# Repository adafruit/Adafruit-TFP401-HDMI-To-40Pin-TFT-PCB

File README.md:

## Adafruit TFP401 HDMI Decoder Breakout PCB
&nbsp; <br />
Click to purchase from the Adafruit Shop:
- [TFP401 HDMI/DVI Decoder to 40-Pin TTL Breakout - Without Touch](https://www.adafruit.com/product/2218)
- [TFP401 HDMI/DVI Decoder to 40-Pin TTL Breakout - With Touch](https://www.adafruit.com/product/2219)

It's a mini HDMI decoder board! So small and simple, you can use this board as an all-in-one display driver for TTL displays, or perhaps decoding HDMI/DVI video for some other project. This breakout features the TFP401 for decoding video, and for the touch version, an AR1100 USB resistive touch screen driver.

The TFP401 is a beefy DVI/HDMI decoder from TI. It can take unencrypted video and pipe out the raw 24-bit color pixel data - HDCP not supported! It will decode any resolution from 25-165MHz pixel clock, basically up to 1080p. We've used this breakout with 800x480 displays, so we have not specifically tested it with higher resolutions. We added a bunch of supporting circuitry like a backlight driver and configured it for running basic TTL display panels such as the ones we have in the shop

There are two versions, one is video only and one is video+touch. 

PCB Files for the Adafruit TFP401 HDMI Decoder Breakout. The format is EagleCAD schematic and board layout

For more details, check out the product pages at
- http://www.adafruit.com/products/2218
- http://www.adafruit.com/products/2219

### License

Adafruit invests time and resources providing this open source design, please support Adafruit and open-source hardware by [purchasing products from Adafruit](https://www.adafruit.com)!

All text above must be included in any redistribution

Designed by Limor Fried/Ladyada for Adafruit Industries.
Creative Commons Attribution/Share-Alike, all text above must be included in any redistribution. 
See license.txt for additional information.

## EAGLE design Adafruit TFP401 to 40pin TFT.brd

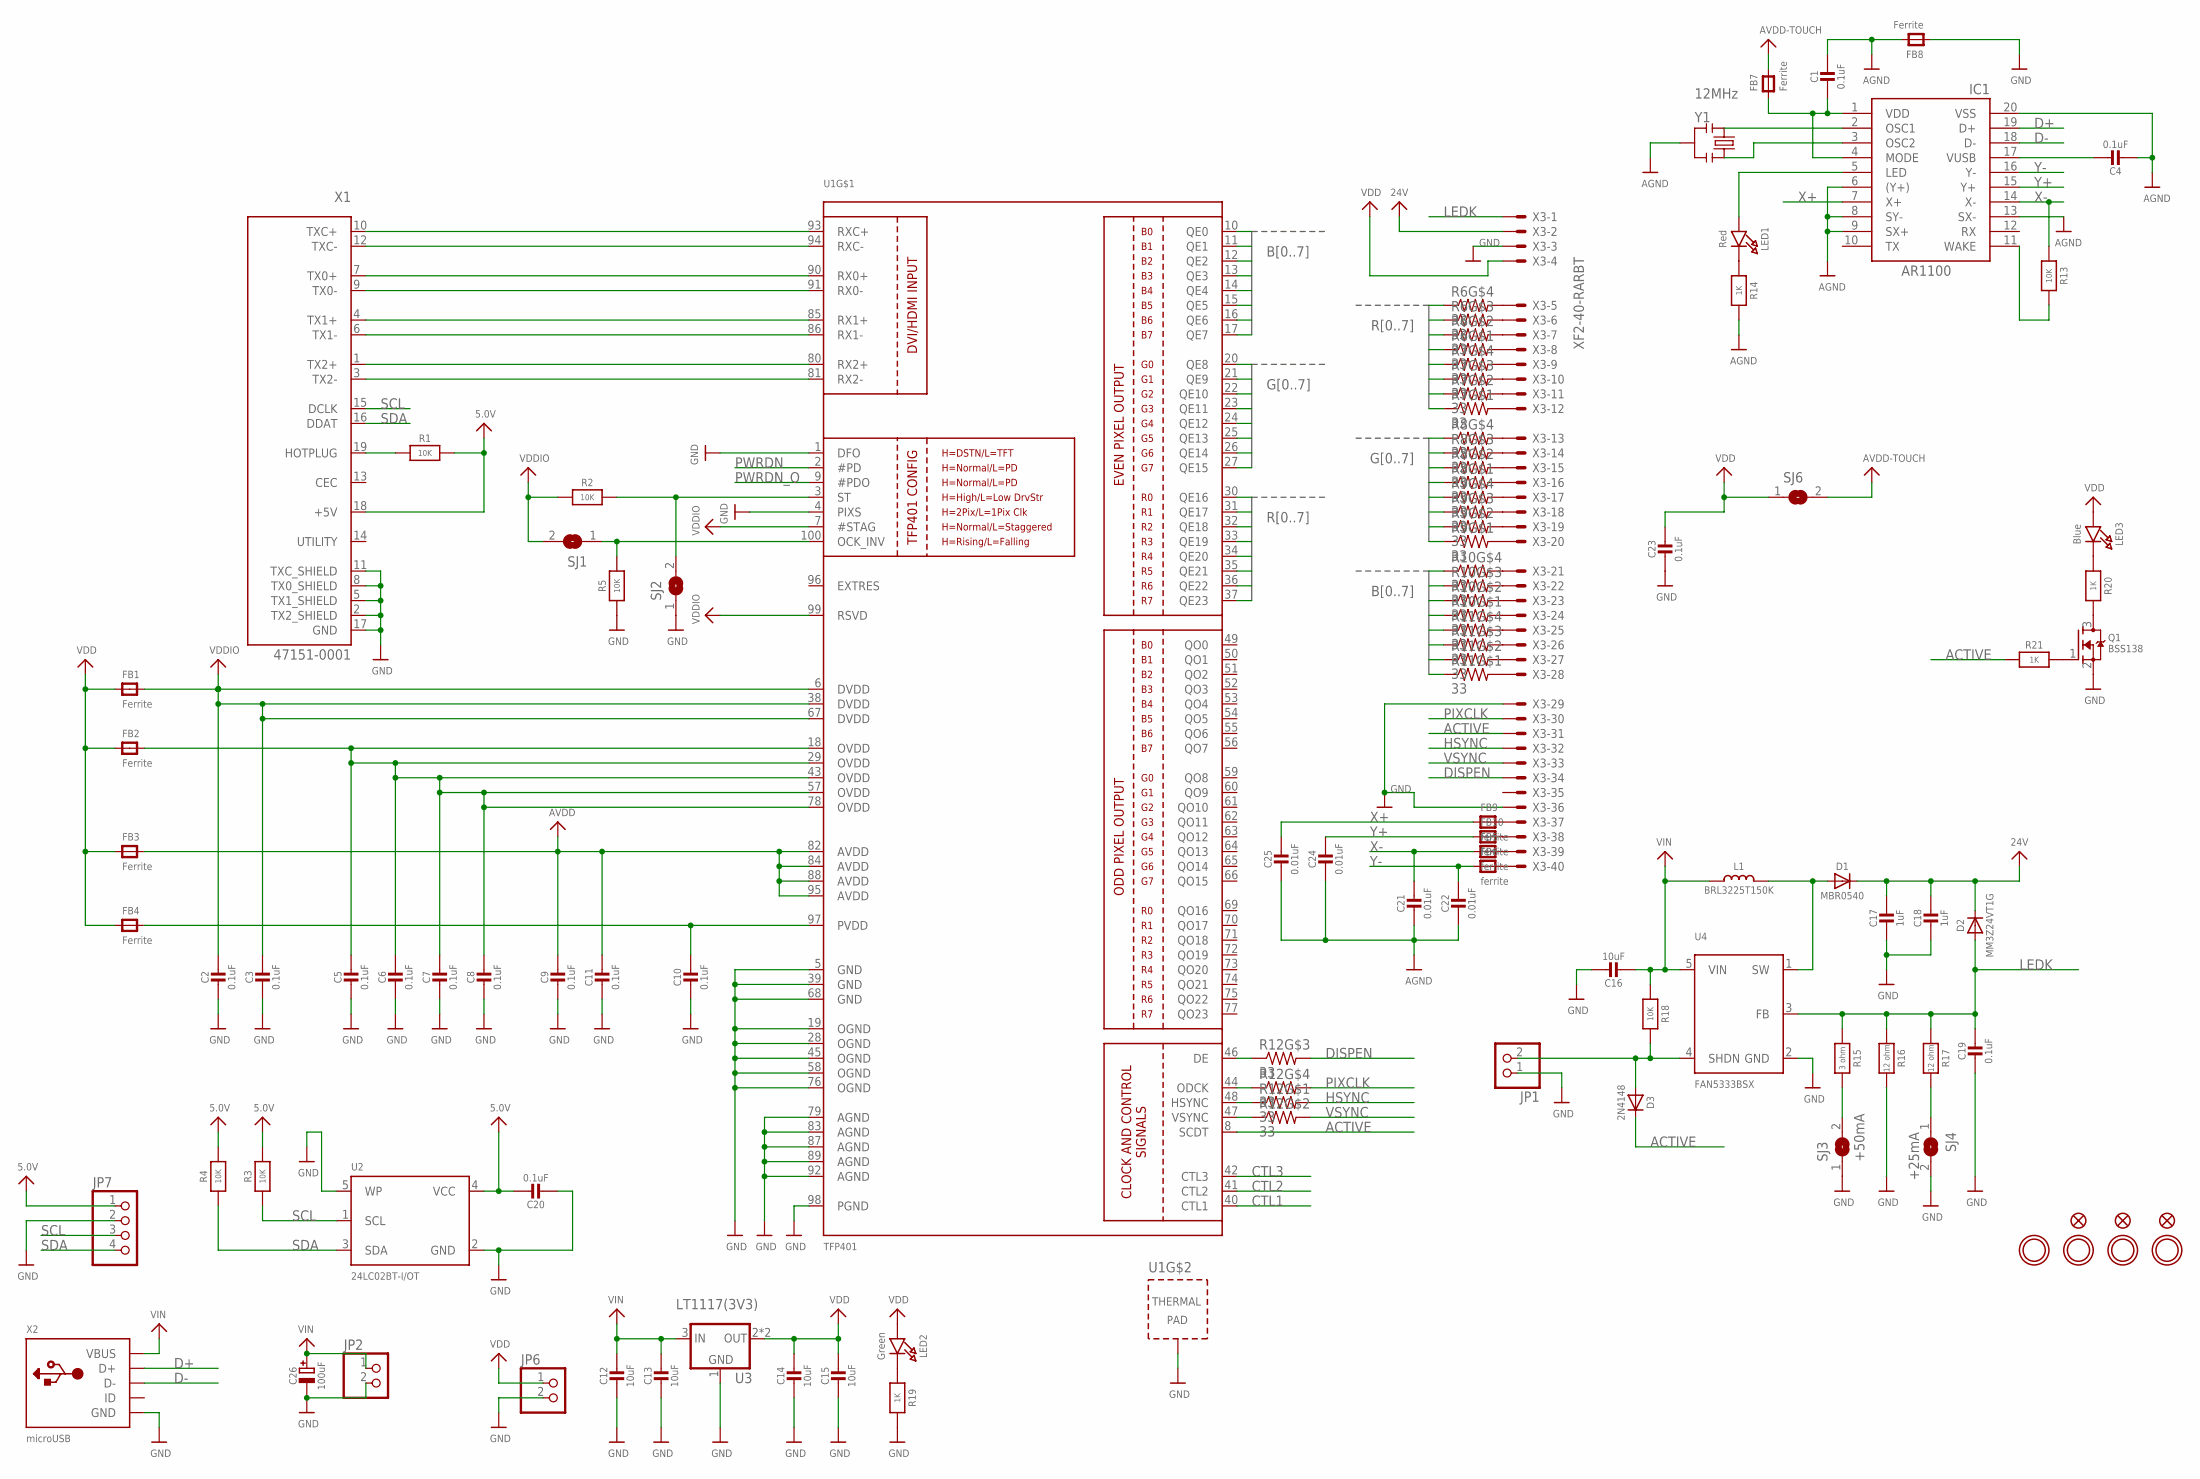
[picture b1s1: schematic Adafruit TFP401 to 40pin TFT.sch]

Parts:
C1, C2, C3, C4, C5, C7, C8, C9, C10, C11, C19, C20, C23: 0.1uF; 0805-NO
C6: 0.1uF; _0805MP
C12, C13, C14, C15, C16: 10uF; 0805-NO
C17, C18: 1uF; 0805-NO
C21, C22, C24, C25: 0.01uF; 0805-NO
C26: 100uF; PANASONIC_C
D1: MBR0540; SOD-123
D2: MM3Z24VT1G; SMADIODE
D3: 2N4148; SOD-323
FB1, FB2, FB3, FB4, FB7, FB8: Ferrite; _0805MP
FB5, FB6, FB9, FB10: ferrite; _0805MP
FID1, FID2, FID3: FIDUCIAL""; FIDUCIAL_1MM
IC1: AR1100_SSOP; TSSOP20-5.3MMBODY
JP1, JP2, JP6: HEADER-1X2ROUND; 1X02_ROUND
JP7: HEADER-1X476MIL; 1X04_ROUND_76
L1: BRL3225T150K; INDUCTOR_5X5MM_NR5040_NOTHERMALS
LED1: Red; CHIPLED_0805_NOOUTLINE
LED2: Green; CHIPLED_0805_NOOUTLINE
LED3: Blue; CHIPLED_0805_NOOUTLINE
Q1: BSS138; SOT23-R
R1, R2, R3, R4, R18: 10K; 0805-NO
R5, R13: 10K; _0805MP
R6, R7, R8, R9, R10, R11, R12: 33; RESPACK_4X0603
R14, R19, R20, R21: 1K; 0805-NO
R15: 3 ohm; 0805-NO
R16, R17: 12 ohm; 0805-NO
SJ1, SJ2: SOLDERJUMPER; SOLDERJUMPER_ARROW_NOPASTE
SJ3: +50mA; SOLDERJUMPER_ARROW_NOPASTE
SJ4: +25mA; SOLDERJUMPER_ARROW_NOPASTE
SJ6: SOLDERJUMPERCLOSED; SOLDERJUMPER_CLOSEDWIRE
U1: TFP401; S-PQFP-G100
U2: 24LC02BT-I/OT; SOT23-5
U3: LT1117(3V3); SOT223-R
U4: FAN5333BSX; SOT23-5
U$31, U$32, U$33, U$34: MOUNTINGHOLE3.0; MOUNTINGHOLE_3.0_PLATED
X1: 47151-0001; HDMI_MOLEX_47151-0001_DIMLAYER
X2: microUSB; 4UCONN_20329
X3: XF2-40-RARBT; 4-1734839-0
Y1: 12MHz; RESONATOR-SMD

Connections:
5.0V: C20.1, JP7.1, R1.2, R3.2, R4.2, U2.4 (VCC), X1.18 (+5V)
24V: C17.1, C18.1, D1.C, D2.C, X3.2 (MS)
ACTIVE: D3.C, R21.1, U1.8 (SCDT), X3.31 (MS)
AGND: C1.1, C4.2, C21.2, C22.2, C24.2, C25.2, FB8.2, IC1.6 ((Y+)), IC1.8 (SY-), IC1.9 (SX+), IC1.13 (SX-), IC1.20 (VSS), R14.2, Y1.2
ASD: R12.3 (1), U1.46 (DE)
AVDD: C9.1, C11.1, FB3.2, U1.82 (AVDD), U1.84 (AVDD), U1.88 (AVDD), U1.95 (AVDD)
AVDD2: FB7.2, SJ6.2
B0: R10.4 (1), U1.10 (QE0)
B1: R10.3 (1), U1.11 (QE1)
B2: R10.2 (1), U1.12 (QE2)
B3: R10.1, U1.13 (QE3)
B4: R11.4 (1), U1.14 (QE4)
B5: R11.3 (1), U1.15 (QE5)
B6: R11.2 (1), U1.16 (QE6)
B7: R11.1, U1.17 (QE7)
CTL1: U1.40 (CTL1)
CTL2: U1.41 (CTL2)
CTL3: U1.42 (CTL3)
CVB: R12.2 (1), U1.47 (VSYNC)
D+: IC1.19 (D+), X2.D+
D-: IC1.18 (D-), X2.D-
DISPEN: R12.6 (2), X3.34 (MS)
G0: R8.4 (1), U1.20 (QE8)
G1: R8.3 (1), U1.21 (QE9)
G2: R8.2 (1), U1.22 (QE10)
G3: R8.1, U1.23 (QE11)
G4: R9.4 (1), U1.24 (QE12)
G5: R9.3 (1), U1.25 (QE13)
G6: R9.2 (1), U1.26 (QE14)
G7: R9.1, U1.27 (QE15)
GND: C2.2, C3.2, C5.2, C6.2, C7.2, C8.2, C9.2, C10.2, C11.2, C12.2, C13.2, C14.2, C15.2, C16.1, C17.2, C18.2, C19.2, C20.2, C23.2, C26.-, FB8.1, JP1.1, JP2.2, JP6.2, JP7.2, Q1.2 (S), R5.1, R16.2, R19.2, SJ2.1, SJ3.1, SJ4.2, U1.1 (DFO), U1.4 (PIXS), U1.5 (GND), U1.19 (OGND), U1.28 (OGND), U1.39 (GND), U1.45 (OGND), U1.58 (OGND), U1.68 (GND), U1.76 (OGND), U1.79 (AGND), U1.83 (AGND), U1.87 (AGND), U1.89 (AGND), U1.92 (AGND), U1.98 (PGND), U1.P$1 (TP), U1.P$2 (TP), U1.P$3 (TP), U1.P$4 (TP), U1.P$5 (TP), U1.P$6 (TP), U1.P$7 (TP), U1.P$8 (TP), U1.P$9 (TP), U1.P$10 (TP), U1.P$11 (TP), U1.P$12 (TP), U1.P$13 (TP), U1.P$14 (TP), U1.P$15 (TP), U1.P$16 (TP), U1.THERMAL (TP), U2.2 (GND), U2.5 (WP), U3.1 (GND), U4.2 (GND), X1.2 (TX2_SHIELD), X1.5 (TX1_SHIELD), X1.8 (TX0_SHIELD), X1.11 (TXC_SHIELD), X1.17 (GND), X1.P$1 (GND), X1.P$2 (GND), X1.P$3 (GND), X1.P$4 (GND), X2.BASE@1 (GND), X2.BASE@2 (GND), X2.GND, X2.SPRT@1 (GND), X2.SPRT@2 (GND), X2.SPRT@3 (GND), X2.SPRT@4 (GND), X3.3 (MS), X3.29 (MS), X3.36 (MS)
HSYNC: R12.8 (2), X3.32 (MS)
LEDK: C19.1, D2.A, R15.1, R16.1, R17.1, U4.3 (FB), X3.1 (MSV)
unnamed: U1.93 (RXC+), X1.10 (TXC+)
unnamed: U1.94 (RXC-), X1.12 (TXC-)
unnamed: U1.90 (RX0+), X1.7 (TX0+)
unnamed: U1.91 (RX0-), X1.9 (TX0-)
unnamed: U1.85 (RX1+), X1.4 (TX1+)
unnamed: U1.86 (RX1-), X1.6 (TX1-)
unnamed: U1.80 (RX2+), X1.1 (TX2+)
unnamed: U1.81 (RX2-), X1.3 (TX2-)
unnamed: R1.1, X1.19 (HOTPLUG)
unnamed: IC1.2 (OSC1), Y1.1
unnamed: IC1.3 (OSC2), Y1.3
unnamed: C4.1, IC1.17 (VUSB)
unnamed: LED2.C, R19.1
unnamed: R6.5 (2), X3.5 (MS)
unnamed: R6.6 (2), X3.6 (MS)
unnamed: R6.7 (2), X3.7 (MS)
unnamed: R6.8 (2), X3.8 (MS)
unnamed: R7.5 (2), X3.9 (MS)
unnamed: R7.6 (2), X3.10 (MS)
unnamed: R7.7 (2), X3.11 (MS)
unnamed: R7.8 (2), X3.12 (MS)
unnamed: R8.5 (2), X3.13 (MS)
unnamed: R8.6 (2), X3.14 (MS)
unnamed: R8.7 (2), X3.15 (MS)
unnamed: R8.8 (2), X3.16 (MS)
unnamed: R9.5 (2), X3.17 (MS)
unnamed: R9.6 (2), X3.18 (MS)
unnamed: R9.7 (2), X3.19 (MS)
unnamed: R9.8 (2), X3.20 (MS)
unnamed: R10.5 (2), X3.21 (MS)
unnamed: R10.6 (2), X3.22 (MS)
unnamed: R10.7 (2), X3.23 (MS)
unnamed: R10.8 (2), X3.24 (MS)
unnamed: R11.5 (2), X3.25 (MS)
unnamed: R11.6 (2), X3.26 (MS)
unnamed: R11.7 (2), X3.27 (MS)
unnamed: C10.1, FB4.2, U1.97 (PVDD)
unnamed: R11.8 (2), X3.28 (MS)
unnamed: IC1.11 (WAKE), R13.2
unnamed: LED1.C, R14.1
unnamed: C5.1, C6.1, C7.1, C8.1, FB2.2, U1.18 (OVDD), U1.29 (OVDD), U1.43 (OVDD), U1.57 (OVDD), U1.78 (OVDD)
unnamed: IC1.5 (LED), LED1.A
unnamed: LED3.C, R20.1
unnamed: Q1.3 (D), R20.2
unnamed: D1.A, L1.P$2 (2), U4.1 (SW)
unnamed: Q1.1 (G), R21.2
unnamed: R15.2, SJ3.2
unnamed: R17.2, SJ4.1
unnamed: D3.A, JP1.2, R18.2, U4.4 (SHDN)
unnamed: FB5.2, X3.39 (MS)
unnamed: FB6.2, X3.40 (MS)
unnamed: C1.2, FB7.1, IC1.1 (VDD), IC1.4 (MODE)
unnamed: FB9.2, X3.37 (MS)
unnamed: FB10.2, X3.38 (MS)
OCK_INV: R5.2, SJ1.1, U1.100 (OCK_INV)
PIXCLK: R12.5 (2), X3.30 (MS)
PWRDN: U1.2 (#PD)
PWRDN_O: U1.9 (#PDO)
R0: R6.4 (1), U1.30 (QE16)
R1: R6.3 (1), U1.31 (QE17)
R2: R6.2 (1), U1.32 (QE18)
R3: R6.1, U1.33 (QE19)
R4: R7.4 (1), U1.34 (QE20)
R5: R7.3 (1), U1.35 (QE21)
R6: R7.2 (1), U1.36 (QE22)
R7: R7.1, U1.37 (QE23)
SCL: JP7.3, R3.1, U2.1 (SCL), X1.15 (DCLK)
SDA: JP7.4, R4.1, U2.3 (SDA), X1.16 (DDAT)
ST: R2.2, SJ2.2, U1.3 (ST)
VDD: C14.1, C15.1, C23.1, FB1.1, FB2.1, FB3.1, FB4.1, JP6.1, LED2.A, LED3.A, SJ6.1, U3.2 (OUT), U3.4 (OUT), X3.4 (MS)
VDDIO: C2.1, C3.1, FB1.2, R2.1, SJ1.2, U1.6 (DVDD), U1.7 (#STAG), U1.38 (DVDD), U1.67 (DVDD), U1.99 (RSVD)
VIN: C12.1, C13.1, C16.2, C26.+, JP2.1, L1.P$1 (1), R18.1, U3.3 (IN), U4.5 (VIN), X2.VBUS
VSYNC: R12.7 (2), X3.33 (MS)
X+: C25.1, FB9.1, IC1.7 (X+)
X-: C21.1, FB5.1, IC1.14 (X-), R13.1
XCV: R12.1, U1.48 (HSYNC)
Y+: C24.1, FB10.1, IC1.15 (Y+)
Y-: C22.1, FB6.1, IC1.16 (Y-)
ZXC: R12.4 (1), U1.44 (ODCK)

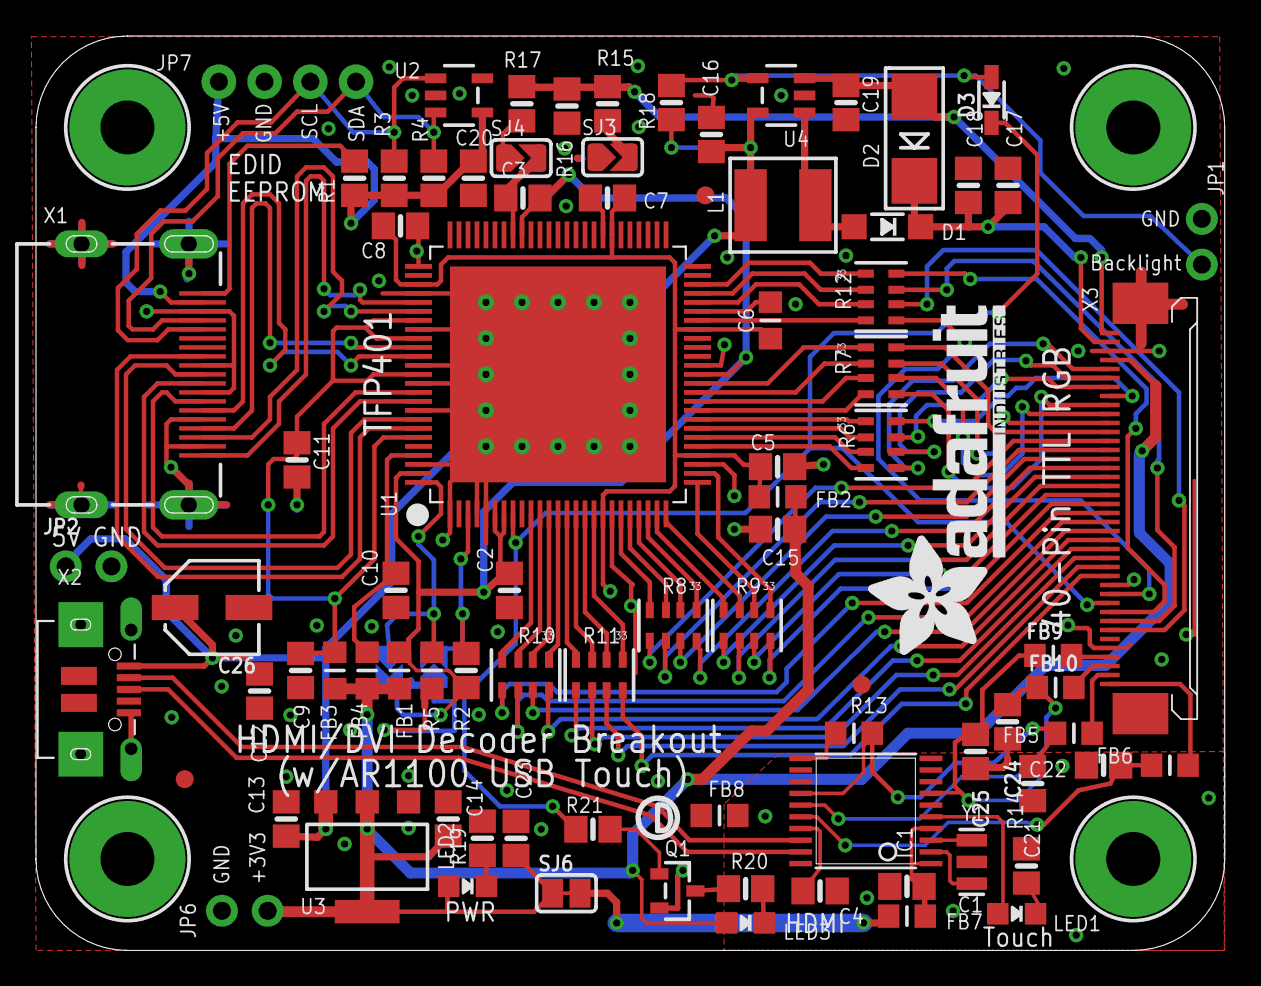
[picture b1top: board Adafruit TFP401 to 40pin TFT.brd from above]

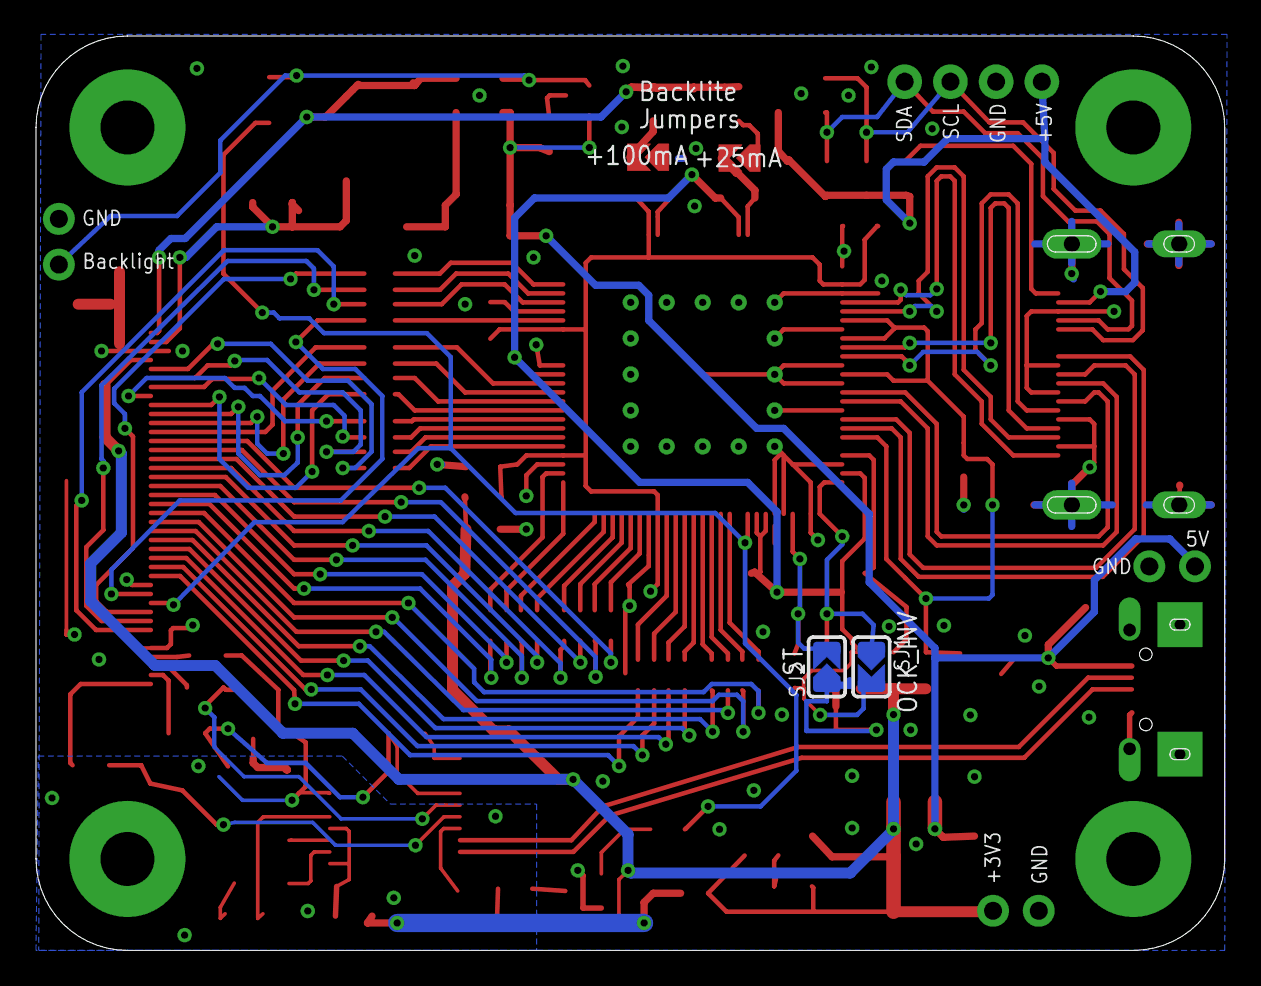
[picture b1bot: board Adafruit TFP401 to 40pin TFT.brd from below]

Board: 2 copper layers, 66.0 x 50.8 mm, 92 parts (2 on the bottom side), 107 nets.

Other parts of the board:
U$80: PCBFEAT-REV-056
U$81: ADAFRUIT_TEXT_20MM

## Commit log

2016-07-04 init

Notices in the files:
parts and their libraries:
microbuilder: This work is placed in the public domain, and may be freely used for commercial and non-commercial work with the following conditions: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
SparkFun: Licensing: CC v3.0 Share-Alike You are welcome to use this library for commercial purposes.
